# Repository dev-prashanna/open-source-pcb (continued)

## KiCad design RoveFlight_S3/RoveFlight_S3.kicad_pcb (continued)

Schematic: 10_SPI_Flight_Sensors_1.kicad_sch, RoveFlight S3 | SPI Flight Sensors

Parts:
C114: 100nF; C_0402_1005Metric_RF_C114; MPN GRM155R71C104KA88D
C115: 100nF; C_0402_1005Metric_RF_C115; MPN GRM155R71C104KA88D
C116: 1uF; C_0402_1005Metric_RF_C116; MPN GRM155R61A105KE15D
C117: 100nF; C_0402_1005Metric_RF_C117; MPN GRM155R71C104KA88D
C118: 100nF; C_0402_1005Metric_RF_C118; MPN GRM155R71C104KA88D
U8: BMI270; Bosch_LGA-14_3x2.5mm_P0.5mm; MPN BMI270
U9: BMP390; BMP390_LGA10; MPN BMP390

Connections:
+3V3_SENS: C114.1, C115.1, C116.1, C117.1, C118.1, U8.5 (VDDIO), U8.8 (VDD), U9.1 (VDDIO), U9.10 (VDD); also elsewhere on the board
BARO_CS: U9.6 (CSB); also elsewhere on the board
GND: C114.2, C115.2, C116.2, C117.2, C118.2, U8.6 (GNDIO), U8.7 (GND), U9.3 (GND), U9.8 (GND), U9.9 (GND); also elsewhere on the board
IMU_CS: U8.12 (CSB); also elsewhere on the board
IMU_INT: U8.4 (INT1); also elsewhere on the board
SPI_MISO: U8.1 (SDO), U9.5 (SDO); also elsewhere on the board
SPI_MOSI: U8.14 (SDI), U9.4 (SDI); also elsewhere on the board
SPI_SCK: U8.13 (SCK), U9.2 (SCK); also elsewhere on the board

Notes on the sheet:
BMI270 primary 4-wire SPI, INT1 data ready. Auxiliary/OIS pins intentionally NC. BMP390 on shared SPI with independent CS; INT unused. Pressure port faces underside. No compass: motor conductors are too close for a defensible uncalibrated onboard heading.

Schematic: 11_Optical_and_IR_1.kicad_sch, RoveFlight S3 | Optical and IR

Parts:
C119: 100nF; C_0402_1005Metric_RF_C119; MPN GRM155R71C104KA88D
C120: 4.7uF; C_0603_1608Metric; MPN GRM188R60J475KE19D
C121: 1uF; C_0402_1005Metric_RF_C121; MPN GRM155R61A105KE15D
C122: 100nF; C_0402_1005Metric_RF_C122; MPN GRM155R71C104KA88D
R121: 10k; R_0402_1005Metric_RF_R121; MPN RC0402FR-071002L
R122: 10k; R_0402_1005Metric_RF_R122; MPN RC0402FR-071002L
R123: 2.2k; R_0402_1005Metric_RF_R123; MPN RC0402FR-072201L
R124: 2.2k; R_0402_1005Metric_RF_R124; MPN RC0402FR-072201L
R125: 100; R_0402_1005Metric_RF_R125; MPN RC0402FR-071000L
U10: VL53L1CXV0FY/1; ST_VL53L1x; MPN VL53L1CXV0FY/1
U11: TSOP75438TT; MPN TSOP75438TT

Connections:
+3V3: R125.1; also elsewhere on the board
+3V3_SENS: C119.1, C120.1, R121.1, R122.1, R123.1, R124.1, U10.1 (AVDDVCSEL), U10.11 (AVDD); also elsewhere on the board
GND: C119.2, C120.2, C121.2, C122.2, U10.2 (AVSSVCSEL), U10.3 (GND), U10.4 (GND), U10.6 (GND), U10.12 (GND), U11.1 (GND), U11.4 (GND); also elsewhere on the board
I2C_SCL: R124.2, U10.10 (SCL); also elsewhere on the board
I2C_SDA: R123.2, U10.9 (SDA); also elsewhere on the board
IR_RX: U11.3 (OUT); also elsewhere on the board
IR_VS: C121.1, C122.1, R125.2, U11.2 (VS)
TOF_INT: R122.2, U10.7 (GPIO1); also elsewhere on the board
TOF_XSHUT: R121.2, U10.5 (XSHUT); also elsewhere on the board

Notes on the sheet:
VL53L1X faces DOWN, I2C 0x29. Firmware must enable 2V8 I/O mode for 3V3 supply. Use near-ground ranging only; sunlight, reflective floors, tilt and prop wash limit reliability. TSOP75438TT is a 38kHz receiver, not proximity sensing. Optical flow is an external SPI module.

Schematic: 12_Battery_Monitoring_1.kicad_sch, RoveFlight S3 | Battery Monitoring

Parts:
C123: 100nF; C_0402_1005Metric_RF_C123; MPN GRM155R71C104KA88D
C124: 100nF; C_0402_1005Metric_RF_C124; MPN GRM155R71C104KA88D
C125: 100nF; C_0402_1005Metric_RF_C125; MPN GRM155R71C104KA88D
R126: 1k; R_0402_1005Metric_RF_R126; MPN RC0402FR-071001L
R127: 100k; R_0402_1005Metric_RF_R127; MPN RC0402FR-071003L
R128: 100k; R_0402_1005Metric_RF_R128; MPN RC0402FR-071003L
R129: 1k; R_0402_1005Metric_RF_R129; MPN RC0402FR-071001L
U12: INA180A2IDBVR; SOT-23-5; MPN INA180A2IDBVR

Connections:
+3V3: C123.1, U12.5 (V+); also elsewhere on the board
BAT_ADC: C125.1, R129.2; also elsewhere on the board
BAT_DIV: R127.2, R128.1, R129.1
BAT_PROTECTED: U12.3 (+); also elsewhere on the board
CURRENT_ADC: C124.1, R126.2; also elsewhere on the board
CURRENT_RAW: R126.1, U12.1
GND: C123.2, C124.2, C125.2, R128.2, U12.2 (GND); also elsewhere on the board
VM: R127.1, U12.4 (-); also elsewhere on the board

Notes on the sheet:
Kelvin sense R1, 5mOhm. INA180A2 gain50: 0.25V/A. ADC1 GPIO1. Battery ADC1 GPIO2, 1:2 divider, RC filter. Calibrate ADC offset/gain in firmware. Fuse is backup short-circuit protection; firmware must implement current and low-battery shutdown.

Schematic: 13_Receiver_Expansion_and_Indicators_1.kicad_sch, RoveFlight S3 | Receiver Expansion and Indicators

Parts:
D7: GREEN; LED_0402_1005Metric; MPN 150040GS73240
J7: RC 3V3; JST_SH_SM04B-SRSS-TB_1x04-1MP_P1.00mm_Horizontal; MPN SM04B-SRSS-TB(LF)(SN)
J8: OPTICAL FLOW SPI; JST_SH_SM07B-SRSS-TB_1x07-1MP_P1.00mm_Horizontal; MPN SM07B-SRSS-TB(LF)(SN)
J9: DEBUG UART; JST_SH_SM06B-SRSS-TB_1x06-1MP_P1.00mm_Horizontal; MPN SM06B-SRSS-TB(LF)(SN)
J10: I2C 3V3; JST_SH_SM04B-SRSS-TB_1x04-1MP_P1.00mm_Horizontal; MPN SM04B-SRSS-TB(LF)(SN)
R130: 1k; R_0402_1005Metric_RF_R130; MPN RC0402FR-071001L
TP1: +3V3; ProbePad; MPN PCB_TEST_PAD
TP2: GND; ProbePad; MPN PCB_TEST_PAD
TP3: VM; ProbePad; MPN PCB_TEST_PAD
TP4: I2C_SDA; ProbePad; MPN PCB_TEST_PAD
TP5: I2C_SCL; ProbePad; MPN PCB_TEST_PAD
TP6: SPI_SCK; ProbePad; MPN PCB_TEST_PAD
TP7: SPI_MOSI; ProbePad; MPN PCB_TEST_PAD
TP8: SPI_MISO; ProbePad; MPN PCB_TEST_PAD
TP9: DEBUG_TX; ProbePad; MPN PCB_TEST_PAD
TP10: DEBUG_RX; ProbePad; MPN PCB_TEST_PAD
TP11: PWM_M1; ProbePad; MPN PCB_TEST_PAD
TP12: PWM_M2; ProbePad; MPN PCB_TEST_PAD
TP13: PWM_M3; ProbePad; MPN PCB_TEST_PAD
TP14: PWM_M4; ProbePad; MPN PCB_TEST_PAD

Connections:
+3V3: J7.2, J8.2, J9.2, TP1.1; also elsewhere on the board
+3V3_SENS: J10.2; also elsewhere on the board
BOOT: J9.6; also elsewhere on the board
DEBUG_RX: J9.4, TP10.1; also elsewhere on the board
DEBUG_TX: J9.3, TP9.1; also elsewhere on the board
EN: J9.5; also elsewhere on the board
FLOW_CS: J8.6; also elsewhere on the board
FLOW_INT: J8.7; also elsewhere on the board
GND: D7.1 (K), J7.1, J8.1, J9.1, J10.1, TP2.1; also elsewhere on the board
I2C_SCL: J10.4, TP5.1; also elsewhere on the board
I2C_SDA: J10.3, TP4.1; also elsewhere on the board
LED_A: D7.2 (A), R130.2
PWM_M1: TP11.1; also elsewhere on the board
PWM_M2: TP12.1; also elsewhere on the board
PWM_M3: TP13.1; also elsewhere on the board
PWM_M4: TP14.1; also elsewhere on the board
RC_RX: J7.3; also elsewhere on the board
RC_TX: J7.4; also elsewhere on the board
SPI_MISO: J8.5, TP8.1; also elsewhere on the board
SPI_MOSI: J8.4, TP7.1; also elsewhere on the board
SPI_SCK: J8.3, TP6.1; also elsewhere on the board
STATUS_LED: R130.1; also elsewhere on the board
VM: TP3.1; also elsewhere on the board

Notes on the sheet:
Receiver: 3V3 UART CRSF/iBUS only, no 5V tolerance or onboard SBUS inverter. External PMW3901 breakout must include its required regulator/level compatibility and lens. SPI test pads/flow connector are 3V3; sensor SPI max10MHz, initial firmware 1MHz.

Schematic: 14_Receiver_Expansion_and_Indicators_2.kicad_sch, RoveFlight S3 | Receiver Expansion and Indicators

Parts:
TP15: SAFE_CLR_N; ProbePad; MPN PCB_TEST_PAD
TP16: ARMED; ProbePad; MPN PCB_TEST_PAD

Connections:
ARMED: TP16.1; also elsewhere on the board
SAFE_CLR_N: TP15.1; also elsewhere on the board

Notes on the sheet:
Receiver: 3V3 UART CRSF/iBUS only, no 5V tolerance or onboard SBUS inverter. External PMW3901 breakout must include its required regulator/level compatibility and lens. SPI test pads/flow connector are 3V3; sensor SPI max10MHz, initial firmware 1MHz.

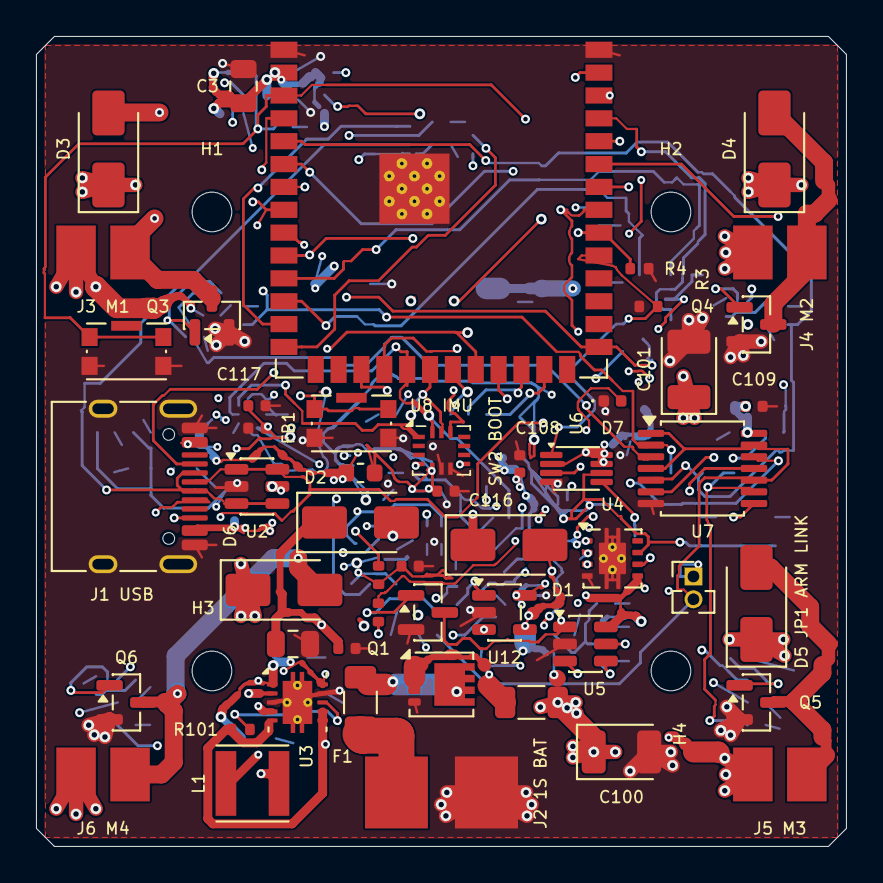
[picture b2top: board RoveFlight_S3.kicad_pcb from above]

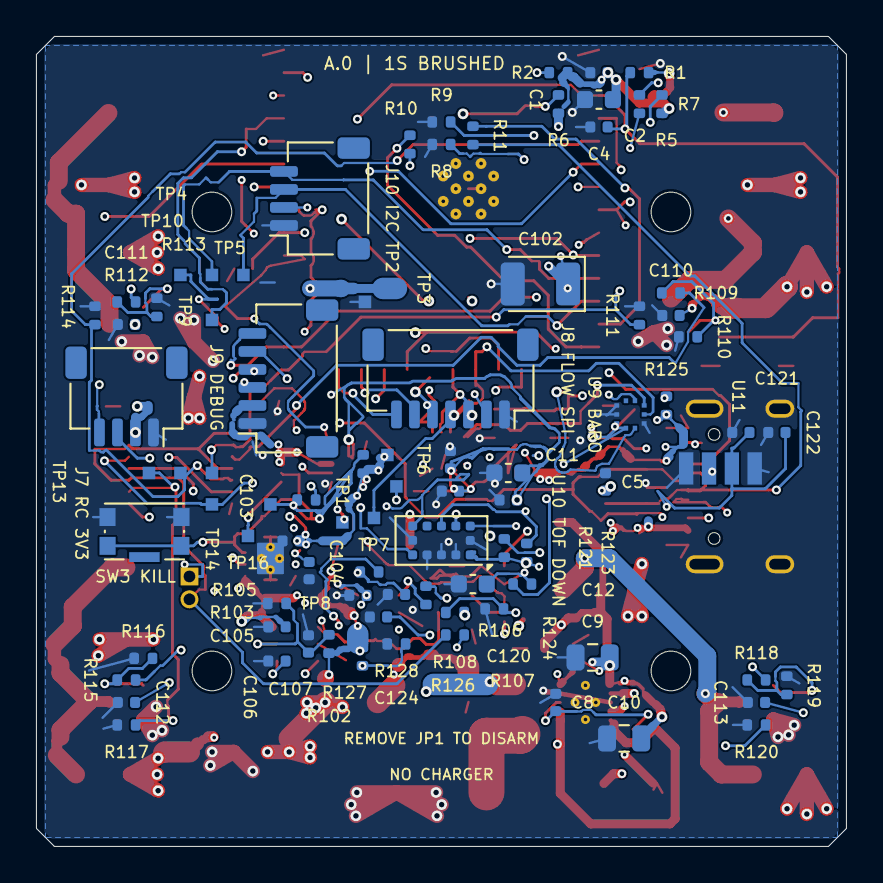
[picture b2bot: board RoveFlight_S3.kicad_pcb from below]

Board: 6 copper layers, 45.0 x 45.0 mm, 142 parts (87 on the bottom side), 71 nets.

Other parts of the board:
H1, H2, H3, H4: MountingHole_2.2mm_M2

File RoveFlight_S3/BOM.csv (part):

Reference,Value,MPN,Manufacturer,Footprint,Section,Datasheet
U1,ESP32-S3-WROOM-1-N8R2,ESP32-S3-WROOM-1-N8R2,Espressif,RoveFlight:ESP32-S3-WROOM-1_Overhang,ESP32S3 Controller,https://www.espressif.com/sites/default/files/documentation/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
C1,100nF,GRM155R71C104KA88D,Murata,RoveFlight:C_0402_1005Metric_RF_C1,ESP32S3 Controller,
C2,10uF,GRM188R60J106ME47D,Murata,Capacitor_SMD:C_0603_1608Metric,ESP32S3 Controller,
C3,22uF,GRM21BR60J226ME39L,Murata,Capacitor_SMD:C_0805_2012Metric,ESP32S3 Controller,
R1,10k,RC0402FR-071002L,Yageo,RoveFlight:R_0402_1005Metric_RF_R1,ESP32S3 Controller,
C4,1uF,GRM155R61A105KE15D,Murata,RoveFlight:C_0402_1005Metric_RF_C4,ESP32S3 Controller,
R2,10k,RC0402FR-071002L,Yageo,RoveFlight:R_0402_1005Metric_RF_R2,ESP32S3 Controller,
SW1,RESET,KMR221GLFS,C&K,Button_Switch_SMD:SW_Push_1P1T-SH_NO_CK_KMR2xxG,ESP32S3 Controller,
SW2,BOOT,KMR221GLFS,C&K,Button_Switch_SMD:SW_Push_1P1T-SH_NO_CK_KMR2xxG,ESP32S3 Controller,
SW3,KILL,KMR221GLFS,C&K,Button_Switch_SMD:SW_Push_1P1T-SH_NO_CK_KMR2xxG,ESP32S3 Controller,
R3,100k,RC0402FR-071003L,Yageo,RoveFlight:R_0402_1005Metric_RF_R3,ESP32S3 Controller,
R4,100k,RC0402FR-071003L,Yageo,RoveFlight:R_0402_1005Metric_RF_R4,ESP32S3 Controller,
R5,10k,RC0402FR-071002L,Yageo,RoveFlight:R_0402_1005Metric_RF_R5,ESP32S3 Controller,
R6,10k,RC0402FR-071002L,Yageo,RoveFlight:R_0402_1005Metric_RF_R6,ESP32S3 Controller,
R7,10k,RC0402FR-071002L,Yageo,RoveFlight:R_0402_1005Metric_RF_R7,ESP32S3 Controller,
J1,USB-C,TYPE-C-31-M-12,HRO,Connector_USB:USB_C_Receptacle_HRO_TYPE-C-31-M-12,USB Programming,
R8,5.1k,RC0402FR-075101L,Yageo,RoveFlight:R_0402_1005Metric_RF_R8,USB Programming,
R9,5.1k,RC0402FR-075101L,Yageo,RoveFlight:R_0402_1005Metric_RF_R9,USB Programming,
R10,22,RC0402FR-0722R0L,Yageo,RoveFlight:R_0402_1005Metric_RF_R10,USB Programming,
R11,22,RC0402FR-0722R0L,Yageo,RoveFlight:R_0402_1005Metric_RF_R11,USB Programming,
U2,USBLC6-2SC6,USBLC6-2SC6,STMicroelectronics,Package_TO_SOT_SMD:SOT-23-6,USB Programming,https://www.st.com/resource/en/datasheet/usblc6-2.pdf
C5,1uF,GRM155R61A105KE15D,Murata,RoveFlight:C_0402_1005Metric_RF_C5,USB Programming,
J2,1S BATTERY,PCB_SOLDER_PADS_20AWG,PCB,RoveFlight:BatteryPads,Battery Power,
F1,5A fuse,0467005.NR,Littelfuse,Fuse:Fuse_1206_3216Metric,Battery Power,
Q1,DMP2008UFG-7,DMP2008UFG-7,Diodes Inc.,Package_SON:Diodes_PowerDI3333-8,Battery Power,https://www.diodes.com/datasheet/download/DMP2008UFG.pdf
R100,5mOhm 1% 0.25W,WSL1206R0050FEA,Vishay,Resistor_SMD:R_1206_3216Metric,Battery Power,
D1,SS14,SS14-13-F,Diodes Inc.,Diode_SMD:D_SMA,Battery Power,
D2,SS14,SS14-13-F,Diodes Inc.,Diode_SMD:D_SMA,Battery Power,
C6,22uF,GRM21BR60J226ME39L,Murata,Capacitor_SMD:C_0805_2012Metric,Battery Power,
C7,100nF,GRM155R71C104KA88D,Murata,RoveFlight:C_0402_1005Metric_RF_C7,Battery Power,
U3,TPS63001DRCR,TPS63001DRCR,Texas Instruments,RoveFlight:Texas_DRC0010J_ThermalVias_RF_U3,Battery Power,https://www.ti.com/lit/ds/symlink/tps63000.pdf
R101,100,RC0402FR-071000L,Yageo,RoveFlight:R_0402_1005Metric_RF_R101,Battery Power,
C8,100nF,GRM155R71C104KA88D,Murata,RoveFlight:C_0402_1005Metric_RF_C8,Battery Power,
C9,22uF,GRM21BR60J226ME39L,Murata,Capacitor_SMD:C_0805_2012Metric,Battery Power,
C10,22uF,GRM21BR60J226ME39L,Murata,Capacitor_SMD:C_0805_2012Metric,Battery Power,
L1,2.2uH 3A,IFSC1515AHER2R2M01,Vishay,Inductor_SMD:L_Vishay_IFSC-1515AH_4x4x1.8mm,Battery Power,
FB1,600R@100MHz,BLM18AG601SN1D,Murata,Inductor_SMD:L_0603_1608Metric,Battery Power,
C11,10uF,GRM188R60J106ME47D,Murata,Capacitor_SMD:C_0603_1608Metric,Battery Power,
C12,100nF,GRM155R71C104KA88D,Murata,RoveFlight:C_0402_1005Metric_RF_C12,Battery Power,
C100,100uF 6.3V polymer,T520B107M006ATE070,KEMET,Capacitor_Tantalum_SMD:CP_EIA-3528-21_Kemet-B,Battery Power,
C101,100uF 6.3V polymer,T520B107M006ATE070,KEMET,Capacitor_Tantalum_SMD:CP_EIA-3528-21_Kemet-B,Battery Power,
C102,100uF 6.3V logic bulk,T520B107M006ATE070,KEMET,Capacitor_Tantalum_SMD:CP_EIA-3528-21_Kemet-B,Battery Power,
U4,TPS3431SDRBR,TPS3431SDRBR,Texas Instruments,Package_DFN_QFN:Texas_DRB0008A,Motor Safety Interlock,https://www.ti.com/lit/ds/symlink/tps3431.pdf
C103,100nF,GRM155R71C104KA88D,Murata,RoveFlight:C_0402_1005Metric_RF_C103,Motor Safety Interlock,
C104,1nF,GRM1555C1H102JA01D,Murata,RoveFlight:C_0402_1005Metric_RF_C104,Motor Safety Interlock,
U5,TPS3808G01DBVR,TPS3808G01DBVR,Texas Instruments,Package_TO_SOT_SMD:SOT-23-6,Motor Safety Interlock,https://www.ti.com/lit/ds/symlink/tps3808.pdf
C105,100nF,GRM155R71C104KA88D,Murata,RoveFlight:C_0402_1005Metric_RF_C105,Motor Safety Interlock,
C106,10nF,GRM155R71H103KA88D,Murata,RoveFlight:C_0402_1005Metric_RF_C106,Motor Safety Interlock,
R102,665k,RC0402FR-076653L,Yageo,RoveFlight:R_0402_1005Metric_RF_R102,Motor Safety Interlock,
R103,100k,RC0402FR-071003L,Yageo,RoveFlight:R_0402_1005Metric_RF_R103,Motor Safety Interlock,
C107,10nF,GRM155R71H103KA88D,Murata,RoveFlight:C_0402_1005Metric_RF_C107,Motor Safety Interlock,
U6,SN74LVC1G74DCUR,SN74LVC1G74DCUR,Texas Instruments,Package_SO:VSSOP-8_2.3x2mm_P0.5mm,Motor Safety Interlock,https://www.ti.com/lit/ds/symlink/sn74lvc1g74.pdf
C108,100nF,GRM155R71C104KA88D,Murata,RoveFlight:C_0402_1005Metric_RF_C108,Motor Safety Interlock,
R104,10k,RC0402FR-071002L,Yageo,RoveFlight:R_0402_1005Metric_RF_R104,Motor Safety Interlock,
R105,1k,RC0402FR-071001L,Yageo,RoveFlight:R_0402_1005Metric_RF_R105,Motor Safety Interlock,
Q2,2N7002,2N7002,Nexperia,Package_TO_SOT_SMD:SOT-23,Motor Safety Interlock,
R106,100k,RC0402FR-071003L,Yageo,RoveFlight:R_0402_1005Metric_RF_R106,Motor Safety Interlock,
R107,1M,RC0402FR-071004L,Yageo,RoveFlight:R_0402_1005Metric_RF_R107,Motor Safety Interlock,
JP1,REMOVE TO DISARM,20021111-00002T4LF,Amphenol,Connector_PinHeader_1.27mm:PinHeader_1x02_P1.27mm_Vertical,Motor Safety Interlock,
R108,10k,RC0402FR-071002L,Yageo,RoveFlight:R_0402_1005Metric_RF_R108,Motor Safety Interlock,
U7,SN74LVC125APWR,SN74LVC125APWR,Texas Instruments,Package_SO:TSSOP-14_4.4x5mm_P0.65mm,Motor Safety Interlock,https://www.ti.com/lit/ds/symlink/sn74lvc125a.pdf
C109,100nF,GRM155R71C104KA88D,Murata,RoveFlight:C_0402_1005Metric_RF_C109,Motor Safety Interlock,
J3,M1 MOTOR,PCB_SOLDER_PADS_24AWG,PCB,RoveFlight:MotorPads,Motor M1,
Q3,AO3400A,AO3400A,Alpha & Omega,Package_TO_SOT_SMD:SOT-23,Motor M1,https://www.aosmd.com/res/data_sheets/AO3400A.pdf
R109,100,RC0402FR-071000L,Yageo,RoveFlight:R_0402_1005Metric_RF_R109,Motor M1,
R110,10k,RC0402FR-071002L,Yageo,RoveFlight:R_0402_1005Metric_RF_R110,Motor M1,
R111,100k,RC0402FR-071003L,Yageo,RoveFlight:R_0402_1005Metric_RF_R111,Motor M1,
D3,SS24,SS24-13-F,Diodes Inc.,Diode_SMD:D_SMA,Motor M1,
C110,100nF,GRM155R71C104KA88D,Murata,RoveFlight:C_0402_1005Metric_RF_C110,Motor M1,
J4,M2 MOTOR,PCB_SOLDER_PADS_24AWG,PCB,RoveFlight:MotorPads,Motor M2,
Q4,AO3400A,AO3400A,Alpha & Omega,Package_TO_SOT_SMD:SOT-23,Motor M2,https://www.aosmd.com/res/data_sheets/AO3400A.pdf
R112,100,RC0402FR-071000L,Yageo,RoveFlight:R_0402_1005Metric_RF_R112,Motor M2,
R113,10k,RC0402FR-071002L,Yageo,RoveFlight:R_0402_1005Metric_RF_R113,Motor M2,
R114,100k,RC0402FR-071003L,Yageo,RoveFlight:R_0402_1005Metric_RF_R114,Motor M2,
D4,SS24,SS24-13-F,Diodes Inc.,Diode_SMD:D_SMA,Motor M2,
C111,100nF,GRM155R71C104KA88D,Murata,RoveFlight:C_0402_1005Metric_RF_C111,Motor M2,
J5,M3 MOTOR,PCB_SOLDER_PADS_24AWG,PCB,RoveFlight:MotorPads,Motor M3,
Q5,AO3400A,AO3400A,Alpha & Omega,Package_TO_SOT_SMD:SOT-23,Motor M3,https://www.aosmd.com/res/data_sheets/AO3400A.pdf
R115,100,RC0402FR-071000L,Yageo,RoveFlight:R_0402_1005Metric_RF_R115,Motor M3,
R116,10k,RC0402FR-071002L,Yageo,RoveFlight:R_0402_1005Metric_RF_R116,Motor M3,
R117,100k,RC0402FR-071003L,Yageo,RoveFlight:R_0402_1005Metric_RF_R117,Motor M3,
D5,SS24,SS24-13-F,Diodes Inc.,Diode_SMD:D_SMA,Motor M3,
C112,100nF,GRM155R71C104KA88D,Murata,RoveFlight:C_0402_1005Metric_RF_C112,Motor M3,
J6,M4 MOTOR,PCB_SOLDER_PADS_24AWG,PCB,RoveFlight:MotorPads,Motor M4,
Q6,AO3400A,AO3400A,Alpha & Omega,Package_TO_SOT_SMD:SOT-23,Motor M4,https://www.aosmd.com/res/data_sheets/AO3400A.pdf
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
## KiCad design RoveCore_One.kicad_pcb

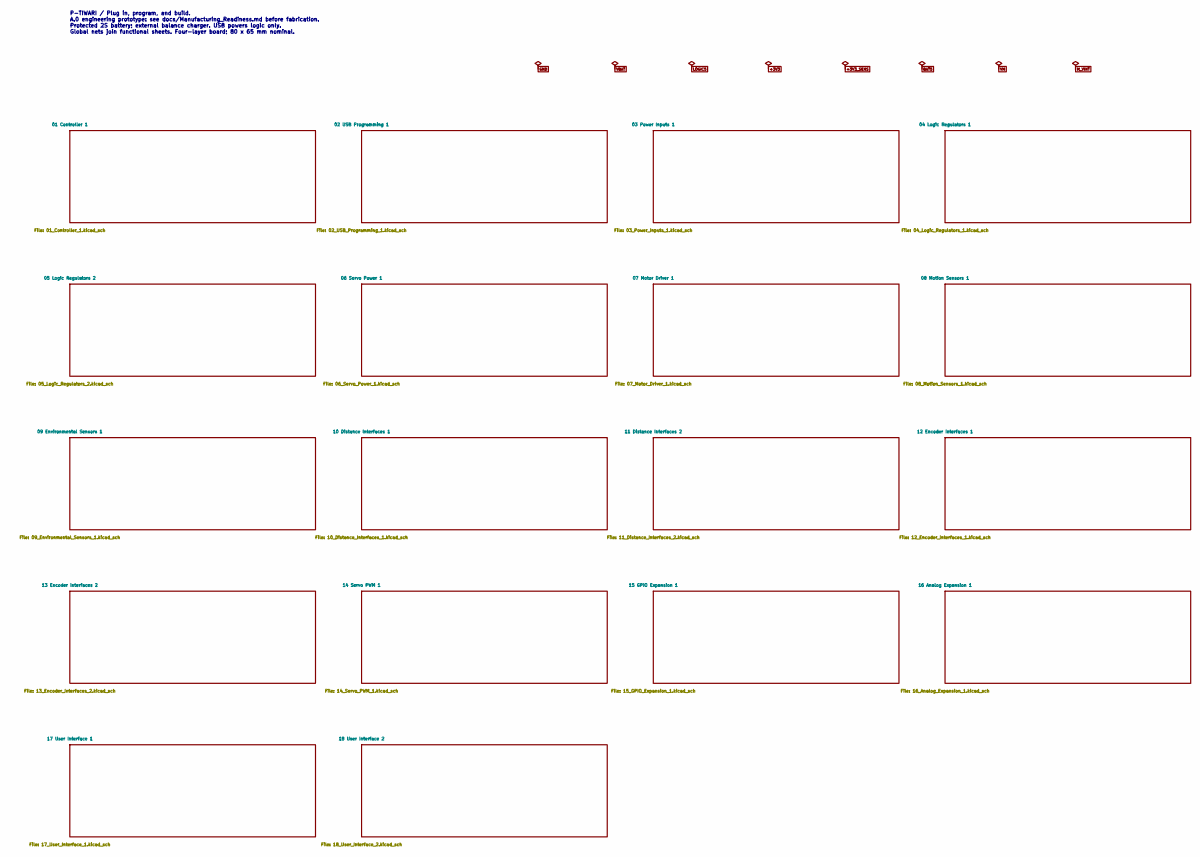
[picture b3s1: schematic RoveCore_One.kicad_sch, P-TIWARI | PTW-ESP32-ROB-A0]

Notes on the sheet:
P-TIWARI / Plug in, program, and build. A.0 engineering prototype: see docs/Manufacturing_Readiness.md before fabrication. Protected 2S battery; external balance charger. USB powers logic only. Global nets join functional sheets. Four-layer board; 80 x 65 mm nominal.

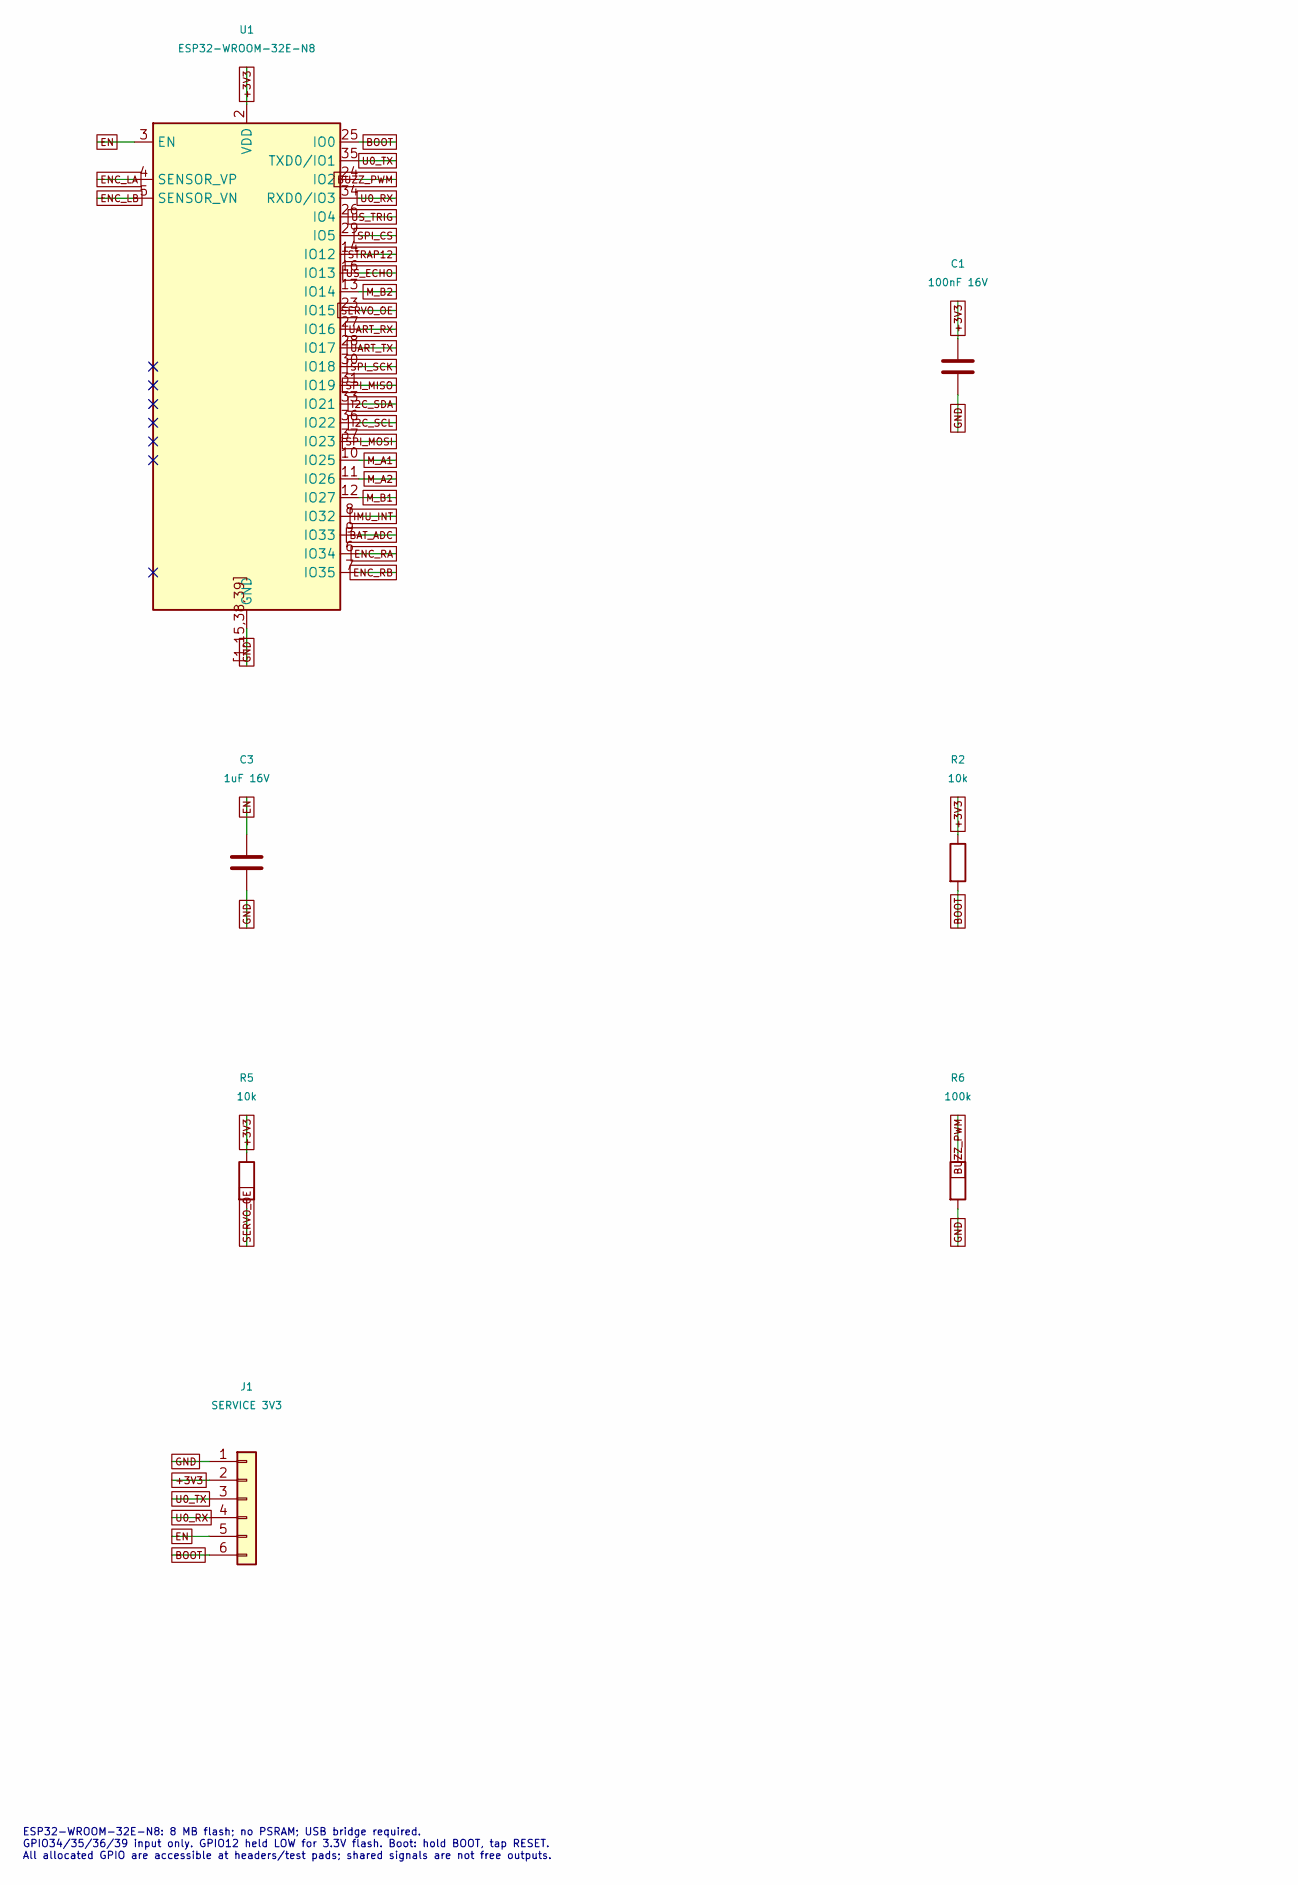
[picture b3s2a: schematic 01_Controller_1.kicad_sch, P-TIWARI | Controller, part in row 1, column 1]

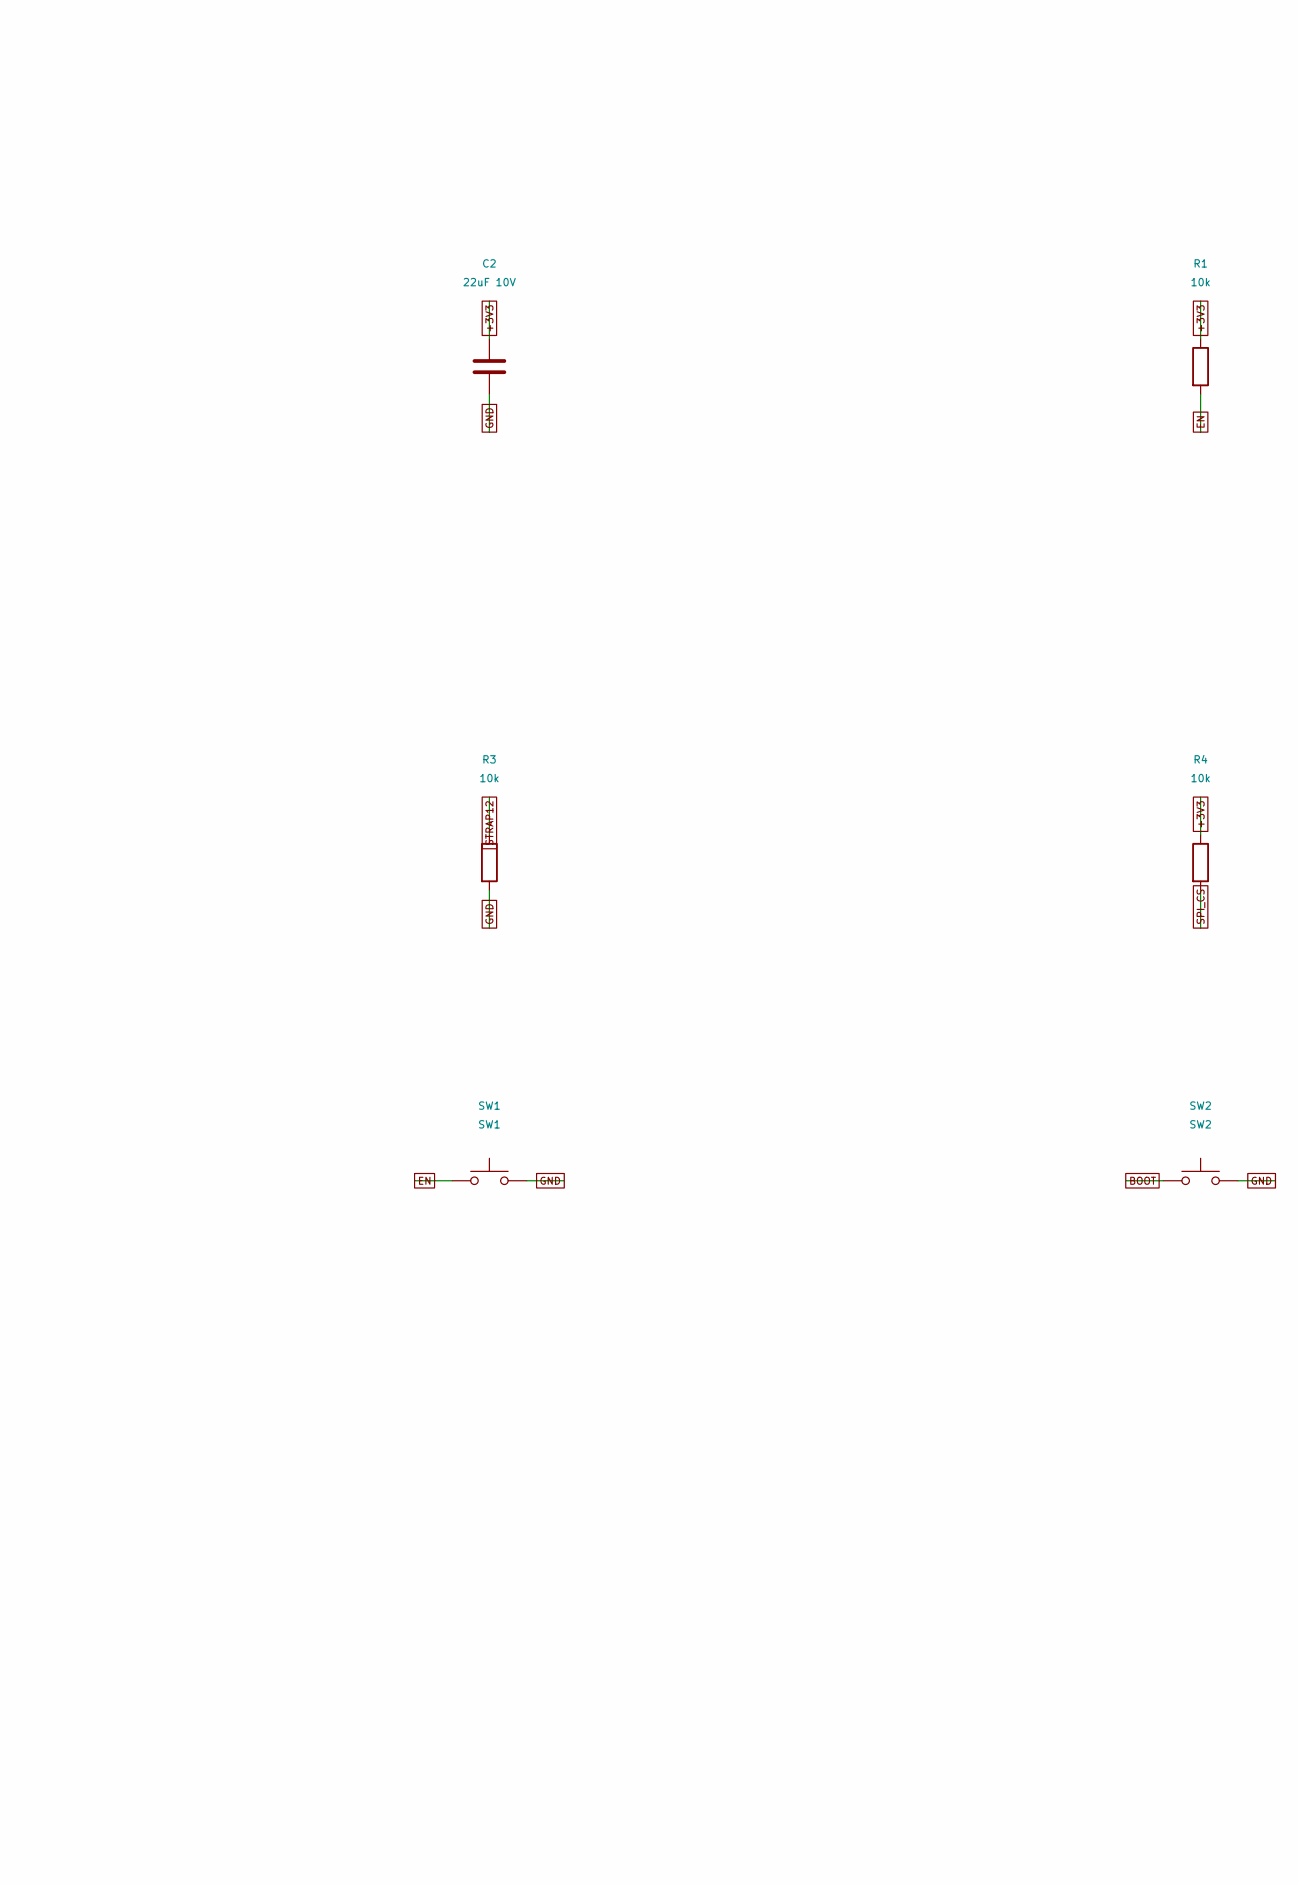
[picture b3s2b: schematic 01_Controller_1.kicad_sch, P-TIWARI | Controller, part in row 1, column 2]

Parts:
C1: 100nF 16V; C_0603_1608Metric; MPN GRM188R71C104KA01D
C2: 22uF 10V; C_0805_2012Metric; MPN GRM21BR61A226ME44L
C3: 1uF 16V; C_0603_1608Metric; MPN GRM188R61C105KA12D
J1: SERVICE 3V3; PinHeader_1x06_P2.00mm_Vertical; MPN M22-2010605
R1, R2, R3, R4, R5: 10k; R_0603_1608Metric; MPN RC0603FR-0710KL
R6: 100k; R_0603_1608Metric; MPN RC0603FR-07100KL
SW1: SW1; SW_Push_1P1T-SH_NO_CK_KMR2xxG; MPN KMR221GLFS
SW2: SW2; SW_Push_1P1T-SH_NO_CK_KMR2xxG; MPN KMR221GLFS
U1: ESP32-WROOM-32E-N8; ESP32-WROOM-32E_Board; MPN ESP32-WROOM-32E-N8

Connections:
+3V3: C1.1, C2.1, J1.2, R1.1, R2.1, R4.1, R5.1, U1.2 (VDD); also elsewhere on the board
BAT_ADC: U1.9 (IO33); also elsewhere on the board
BOOT: J1.6, R2.2, SW2.1, U1.25 (IO0); also elsewhere on the board
BUZZ_PWM: R6.1, U1.24 (IO2); also elsewhere on the board
EN: C3.1, J1.5, R1.2, SW1.1, U1.3 (EN); also elsewhere on the board
ENC_LA: U1.4 (SENSOR_VP); also elsewhere on the board
ENC_LB: U1.5 (SENSOR_VN); also elsewhere on the board
ENC_RA: U1.6 (IO34); also elsewhere on the board
ENC_RB: U1.7 (IO35); also elsewhere on the board
GND: C1.2, C2.2, C3.2, J1.1, R3.2, R6.2, SW1.2, SW2.2, U1.1, U1.15, U1.38, U1.39, U1.[1,15,38,39] (GND); also elsewhere on the board
I2C_SCL: U1.36 (IO22); also elsewhere on the board
I2C_SDA: U1.33 (IO21); also elsewhere on the board
IMU_INT: U1.8 (IO32); also elsewhere on the board
M_A1: U1.10 (IO25); also elsewhere on the board
M_A2: U1.11 (IO26); also elsewhere on the board
M_B1: U1.12 (IO27); also elsewhere on the board
M_B2: U1.13 (IO14); also elsewhere on the board
SERVO_OE: R5.2, U1.23 (IO15); also elsewhere on the board
SPI_CS: R4.2, U1.29 (IO5); also elsewhere on the board
SPI_MISO: U1.31 (IO19); also elsewhere on the board
SPI_MOSI: U1.37 (IO23); also elsewhere on the board
SPI_SCK: U1.30 (IO18); also elsewhere on the board
STRAP12: R3.1, U1.14 (IO12)
U0_RX: J1.4, U1.34 (RXD0/IO3); also elsewhere on the board
U0_TX: J1.3, U1.35 (TXD0/IO1); also elsewhere on the board
UART_RX: U1.27 (IO16); also elsewhere on the board
UART_TX: U1.28 (IO17); also elsewhere on the board
US_ECHO: U1.16 (IO13); also elsewhere on the board
US_TRIG: U1.26 (IO4); also elsewhere on the board

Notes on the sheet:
ESP32-WROOM-32E-N8: 8 MB flash; no PSRAM; USB bridge required. GPIO34/35/36/39 input only. GPIO12 held LOW for 3.3V flash. Boot: hold BOOT, tap RESET. All allocated GPIO are accessible at headers/test pads; shared signals are not free outputs.
